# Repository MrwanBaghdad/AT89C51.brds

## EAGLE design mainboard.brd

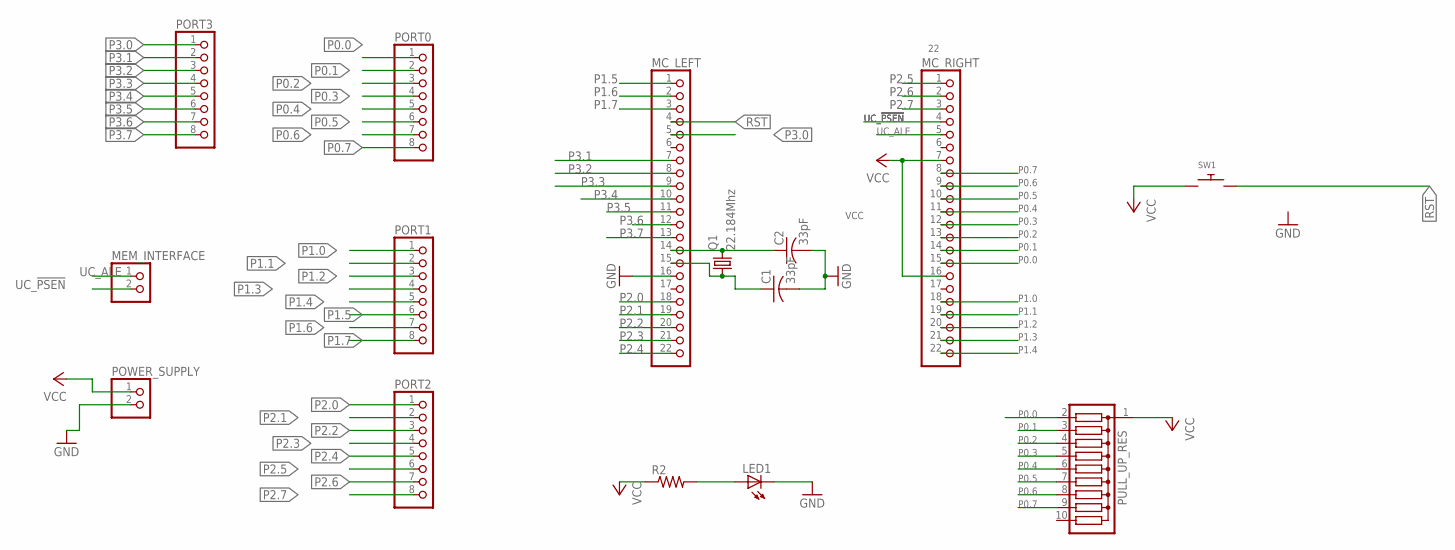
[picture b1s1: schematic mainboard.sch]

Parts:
C1, C2: 33pF; C050-025X075
LED1: LED3MM
MC_LEFT: PINHD-1X22; 1X22
MC_RIGHT: PINHD-1X22; 1X22
MEM_INTERFACE: PINHD-1X2; 1X02
PORT0, PORT1, PORT2, PORT3: PINHD-1X8; 1X08
POWER_SUPPLY: PINHD-1X2; 1X02
PULL_UP_RES: G09R; SIL10
Q1: 22.184Mhz; HC49/S
R2: R-US_0204/5; 0204/5
SW1: SWITCH_PUSHBUTTONEVQ-PE; TACT_PANA-EVQ

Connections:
GND: C1.2, C2.2, LED1.K (C), MC_LEFT.16, POWER_SUPPLY.2
unnamed: C2.1, MC_LEFT.14, Q1.2
unnamed: C1.1, MC_LEFT.15, Q1.1
unnamed: LED1.A, R2.2
P0.0: MC_RIGHT.15, PORT0.1, PULL_UP_RES.2
P0.1: MC_RIGHT.14, PORT0.2, PULL_UP_RES.3
P0.2: MC_RIGHT.13, PORT0.3, PULL_UP_RES.4
P0.3: MC_RIGHT.12, PORT0.4, PULL_UP_RES.5
P0.4: MC_RIGHT.11, PORT0.5, PULL_UP_RES.6
P0.5: MC_RIGHT.10, PORT0.6, PULL_UP_RES.7
P0.6: MC_RIGHT.9, PORT0.7, PULL_UP_RES.8
P0.7: MC_RIGHT.8, PORT0.8, PULL_UP_RES.9
P1.0: MC_RIGHT.18, PORT1.1
P1.1: MC_RIGHT.19, PORT1.2
P1.2: MC_RIGHT.20, PORT1.3
P1.3: MC_RIGHT.21, PORT1.4
P1.4: MC_RIGHT.22, PORT1.5
P1.5: MC_LEFT.1, PORT1.6
P1.6: MC_LEFT.2, PORT1.7
P1.7: MC_LEFT.3, PORT1.8
P2.0: MC_LEFT.18, PORT2.1
P2.1: MC_LEFT.19, PORT2.2
P2.2: MC_LEFT.20, PORT2.3
P2.3: MC_LEFT.21, PORT2.4
P2.4: MC_LEFT.22, PORT2.5
P2.5: MC_RIGHT.1, PORT2.6
P2.6: MC_RIGHT.2, PORT2.7
P2.7: MC_RIGHT.3, PORT2.8
P3.0: MC_LEFT.5, PORT3.1
P3.1: MC_LEFT.7, PORT3.2
P3.2: MC_LEFT.8, PORT3.3
P3.3: MC_LEFT.9, PORT3.4
P3.4: MC_LEFT.10, PORT3.5
P3.5: MC_LEFT.11, PORT3.6
P3.6: MC_LEFT.12, PORT3.7
P3.7: MC_LEFT.13, PORT3.8
RST: MC_LEFT.4, SW1.P$2
UC_!PSEN: MC_RIGHT.4, MEM_INTERFACE.2
UC_ALE: MC_RIGHT.5, MEM_INTERFACE.1
VCC: MC_RIGHT.7, MC_RIGHT.16, POWER_SUPPLY.1, PULL_UP_RES.1, R2.1, SW1.P$1

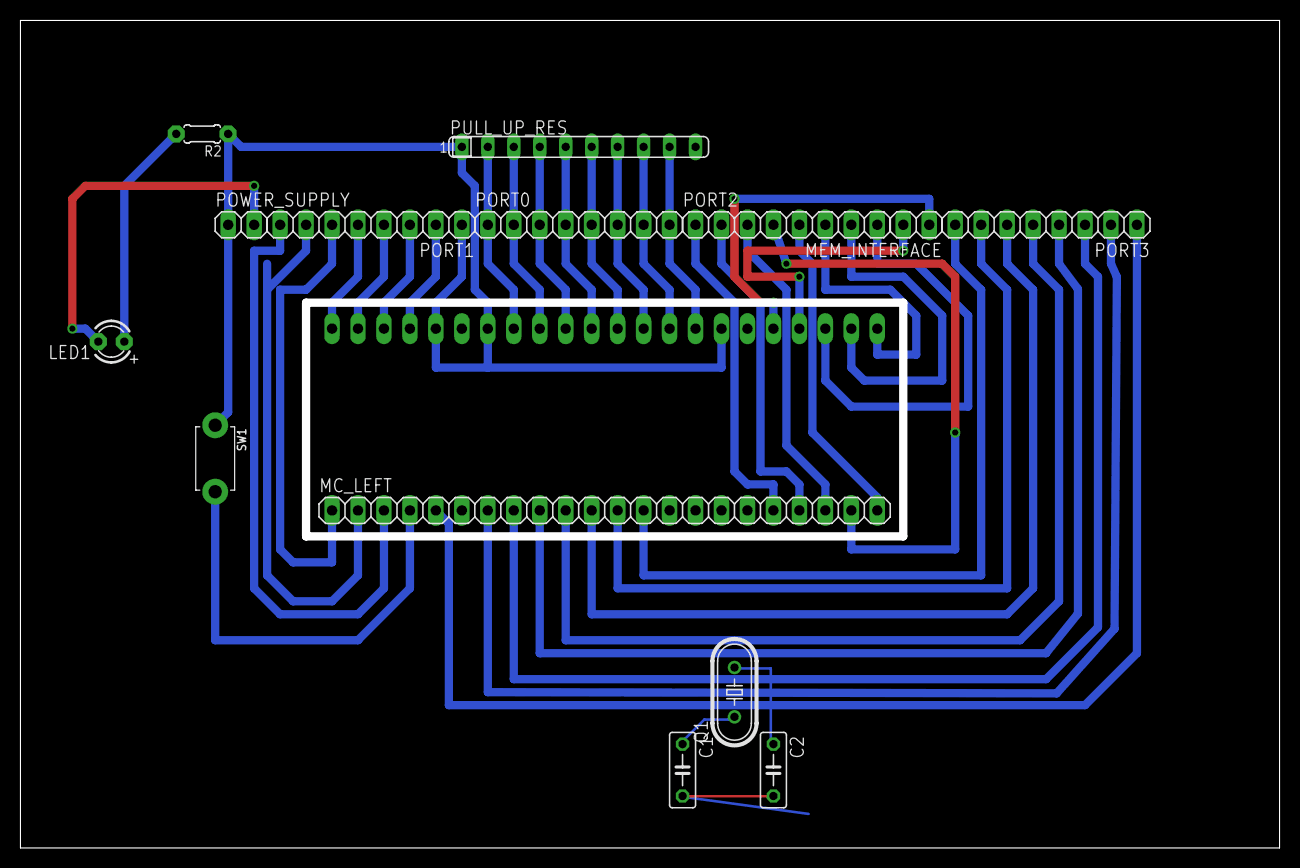
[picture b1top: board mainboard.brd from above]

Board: 2 copper layers, 123.2 x 81.0 mm, 15 parts (1 on the bottom side), 40 nets.

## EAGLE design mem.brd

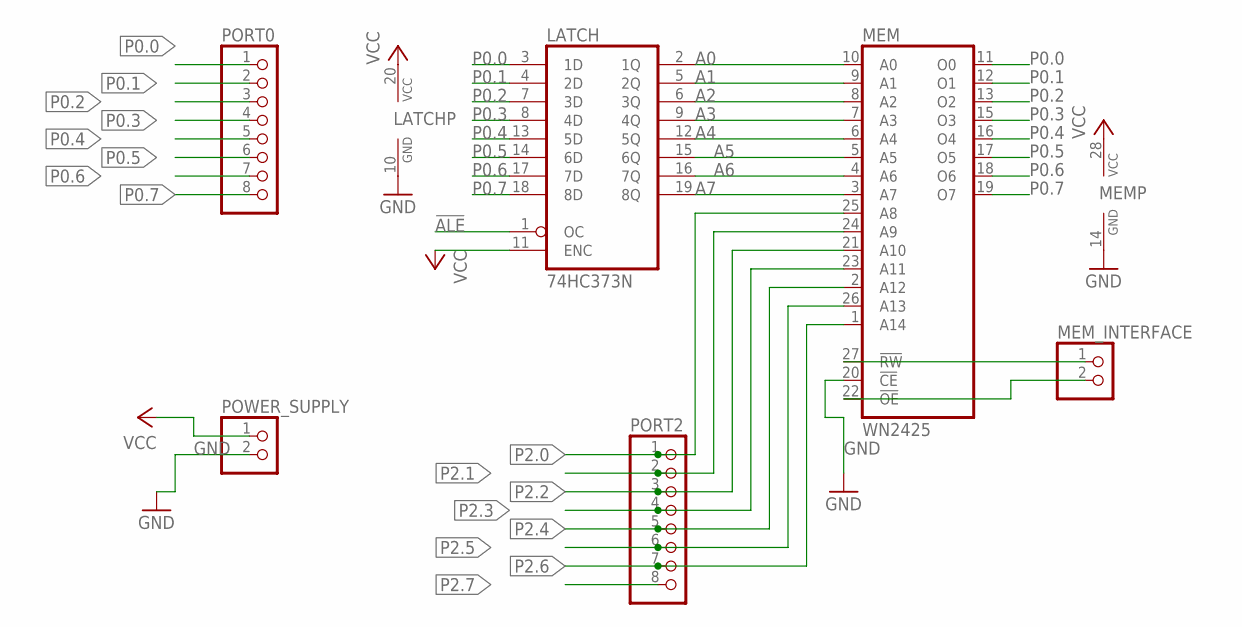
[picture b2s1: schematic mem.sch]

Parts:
LATCH: 74HC373N; DIL20
MEM: WN2425; DIL28
MEM_INTERFACE: PINHD-1X2; 1X02
PORT0, PORT2: PINHD-1X8; 1X08
POWER_SUPPLY: PINHD-1X2; 1X02

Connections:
!ALE: LATCH.1 (OC)
A0: LATCH.2 (1Q), MEM.10 (A0)
A1: LATCH.5 (2Q), MEM.9 (A1)
A2: LATCH.6 (3Q), MEM.8 (A2)
A3: LATCH.9 (4Q), MEM.7 (A3)
A4: LATCH.12 (5Q), MEM.6 (A4)
A5: LATCH.15 (6Q), MEM.5 (A5)
A6: LATCH.16 (7Q), MEM.4 (A6)
A7: LATCH.19 (8Q), MEM.3 (A7)
GND: LATCH.10 (GND), MEM.14 (GND), MEM.20 (!CE), POWER_SUPPLY.2
P0.0: LATCH.3 (1D), MEM.11 (O0), PORT0.1
P0.1: LATCH.4 (2D), MEM.12 (O1), PORT0.2
P0.2: LATCH.7 (3D), MEM.13 (O2), PORT0.3
P0.3: LATCH.8 (4D), MEM.15 (O3), PORT0.4
P0.4: LATCH.13 (5D), MEM.16 (O4), PORT0.5
P0.5: LATCH.14 (6D), MEM.17 (O5), PORT0.6
P0.6: LATCH.17 (7D), MEM.18 (O6), PORT0.7
P0.7: LATCH.18 (8D), MEM.19 (O7), PORT0.8
P2.0: MEM.25 (A8), PORT2.1
P2.1: MEM.24 (A9), PORT2.2
P2.2: MEM.21 (A10), PORT2.3
P2.3: MEM.23 (A11), PORT2.4
P2.4: MEM.2 (A12), PORT2.5
P2.5: MEM.26 (A13), PORT2.6
P2.6: MEM.1 (A14), PORT2.7
P2.7: PORT2.8
UC_ALE: MEM.27 (!RW), MEM_INTERFACE.1
UC_PSEN: MEM.22 (!OE), MEM_INTERFACE.2
VCC: LATCH.11 (ENC), LATCH.20 (VCC), MEM.28 (VCC), POWER_SUPPLY.1

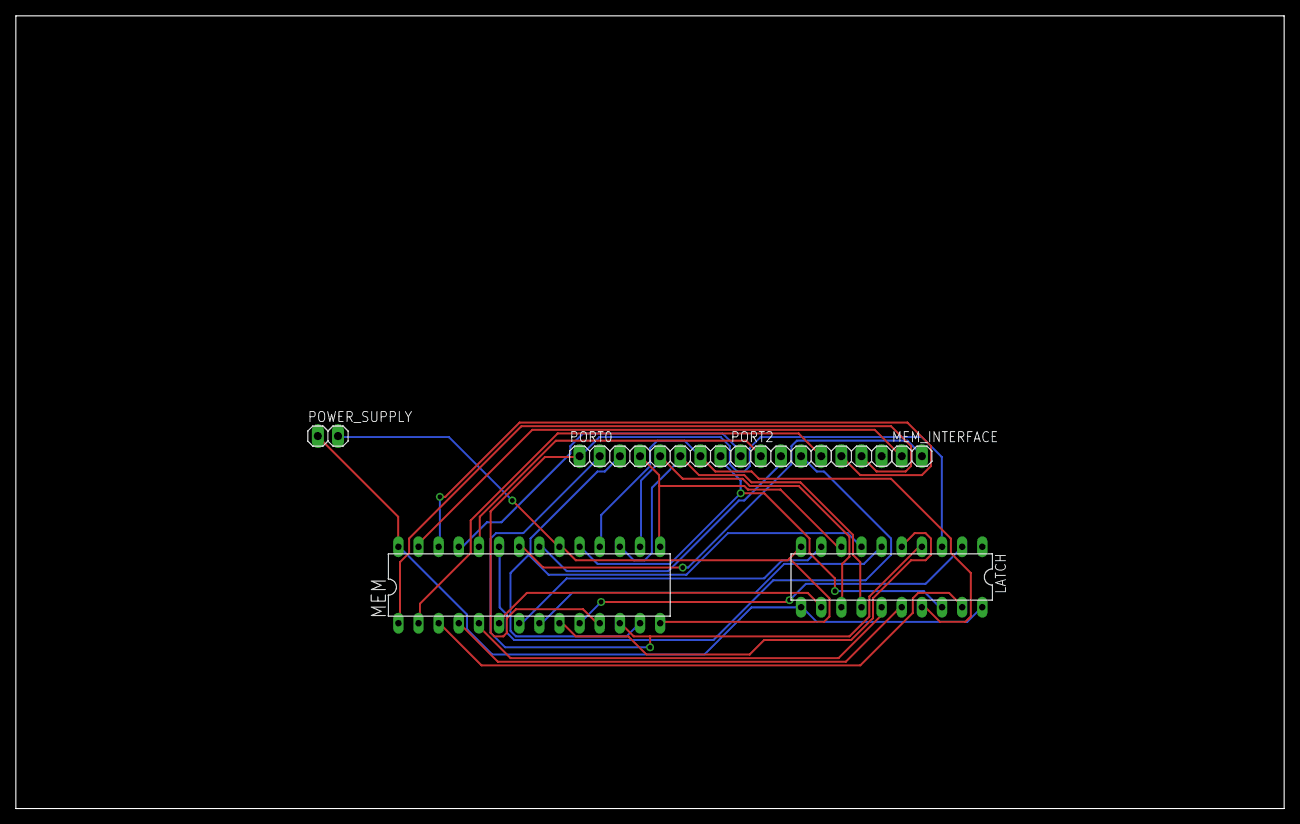
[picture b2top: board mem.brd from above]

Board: 2 copper layers, 160.0 x 100.0 mm, 6 parts (0 on the bottom side), 27 nets.

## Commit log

2017-05-04 init repo
